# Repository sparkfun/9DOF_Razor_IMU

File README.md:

SparkFun 9DoF Razor IMU M0
========================================

[*SparkFun 9DoF Razor IMU M0 (SEN-14001)*](https://www.sparkfun.com/products/14001)

The [SparkFun 9DoF Razor IMU M0](https://www.sparkfun.com/products/14001) combines a [SAMD21](https://www.sparkfun.com/products/13664) microprocessor with an [MPU-9250](https://www.sparkfun.com/products/13762) 9DoF (nine degrees of freedom) sensor to create a tiny, re-programmable, multi-purpose inertial measurement unit (IMU). It can be programmed to monitor and log motion, transmit Euler angles over a serial port, or to even act as a step-counting pedometer.

The 9DoF Razor's MPU-9250 features three, three-axis sensors -- an accelerometer, gyroscope, and magnetometer -- which gives it the ability to sense linear acceleration, angular rotation velocity, and magnetic field vector's. The on-board microprocessor -- Atmel's [SAMD21G18A](http://www.atmel.com/devices/ATSAMD21G18.aspx) -- is an Arduino-compatible, 32-bit ARM Cortex-M0+ microcontroller also featured on the [Arduino Zero](https://www.arduino.cc/en/Main/ArduinoBoardZero) and [SAMD21 Mini Breakout](https://www.sparkfun.com/products/13664) boards.

Repository Contents
-------------------

* **/Documentation** - Data sheets, additional product information
* **/Firmware** - Example code 
* **/Hardware** - Eagle design files (.brd, .sch)
* **/Libraries** - Libraries for use with the 9DoF Razor IMU M0
* **/Production Files** - Production panel files (.brd)

Documentation
--------------
* **[SparkFun MPU-9250 DMP Arduino Library](https://github.com/sparkfun/SparkFun_MPU-9250-DMP_Arduino_Library)** - Arduino library for the 9DoF Razor IMU M0's MPU-9250, enabling the 9DoF's digital motion processor (DMP).
* **[Hookup Guide](https://learn.sparkfun.com/tutorials/9dof-razor-imu-m0-hookup-guide)** - Basic hookup guide for the 9DoF Razor IMU M0.
* **[SparkFun Fritzing repo](https://github.com/sparkfun/Fritzing_Parts)** - Fritzing diagrams for SparkFun products.
* **[SparkFun 3D Model repo](https://github.com/sparkfun/3D_Models)** - 3D models of SparkFun products. 

Product Versions
----------------
* [SparkFun 9DoF Razor IMU M0 (SEN-14001)](https://www.sparkfun.com/products/14001)- Latest release.
* [SparkFun 9DoF Razor IMU (SEN-10736)](https://www.sparkfun.com/products/retired/10736) - Initial release, featuring an ATmega328, ADXL345 (accelerometer), ITG-3200 (gyroscope), and HMC5883L (magnetometer).

Version History
---------------
* [V_3.0](https://github.com/sparkfun/9DOF_Razor_IMU/releases/tag/V_3.0) - Hardware and firmware files for version 3.0 -- released as SEN-14001.
* [V_2.3](https://github.com/sparkfun/9DOF_Razor_IMU/releases/tag/V_2.3) - Hardware and firmware design files for version 2.3 -- released as SEN-10736.

License Information
-------------------

This product is _**open source**_! 

Please review the LICENSE.md file for license information. 

If you have any questions or concerns on licensing, please contact techsupport@sparkfun.com.

Distributed as-is; no warranty is given.

- Your friends at SparkFun.

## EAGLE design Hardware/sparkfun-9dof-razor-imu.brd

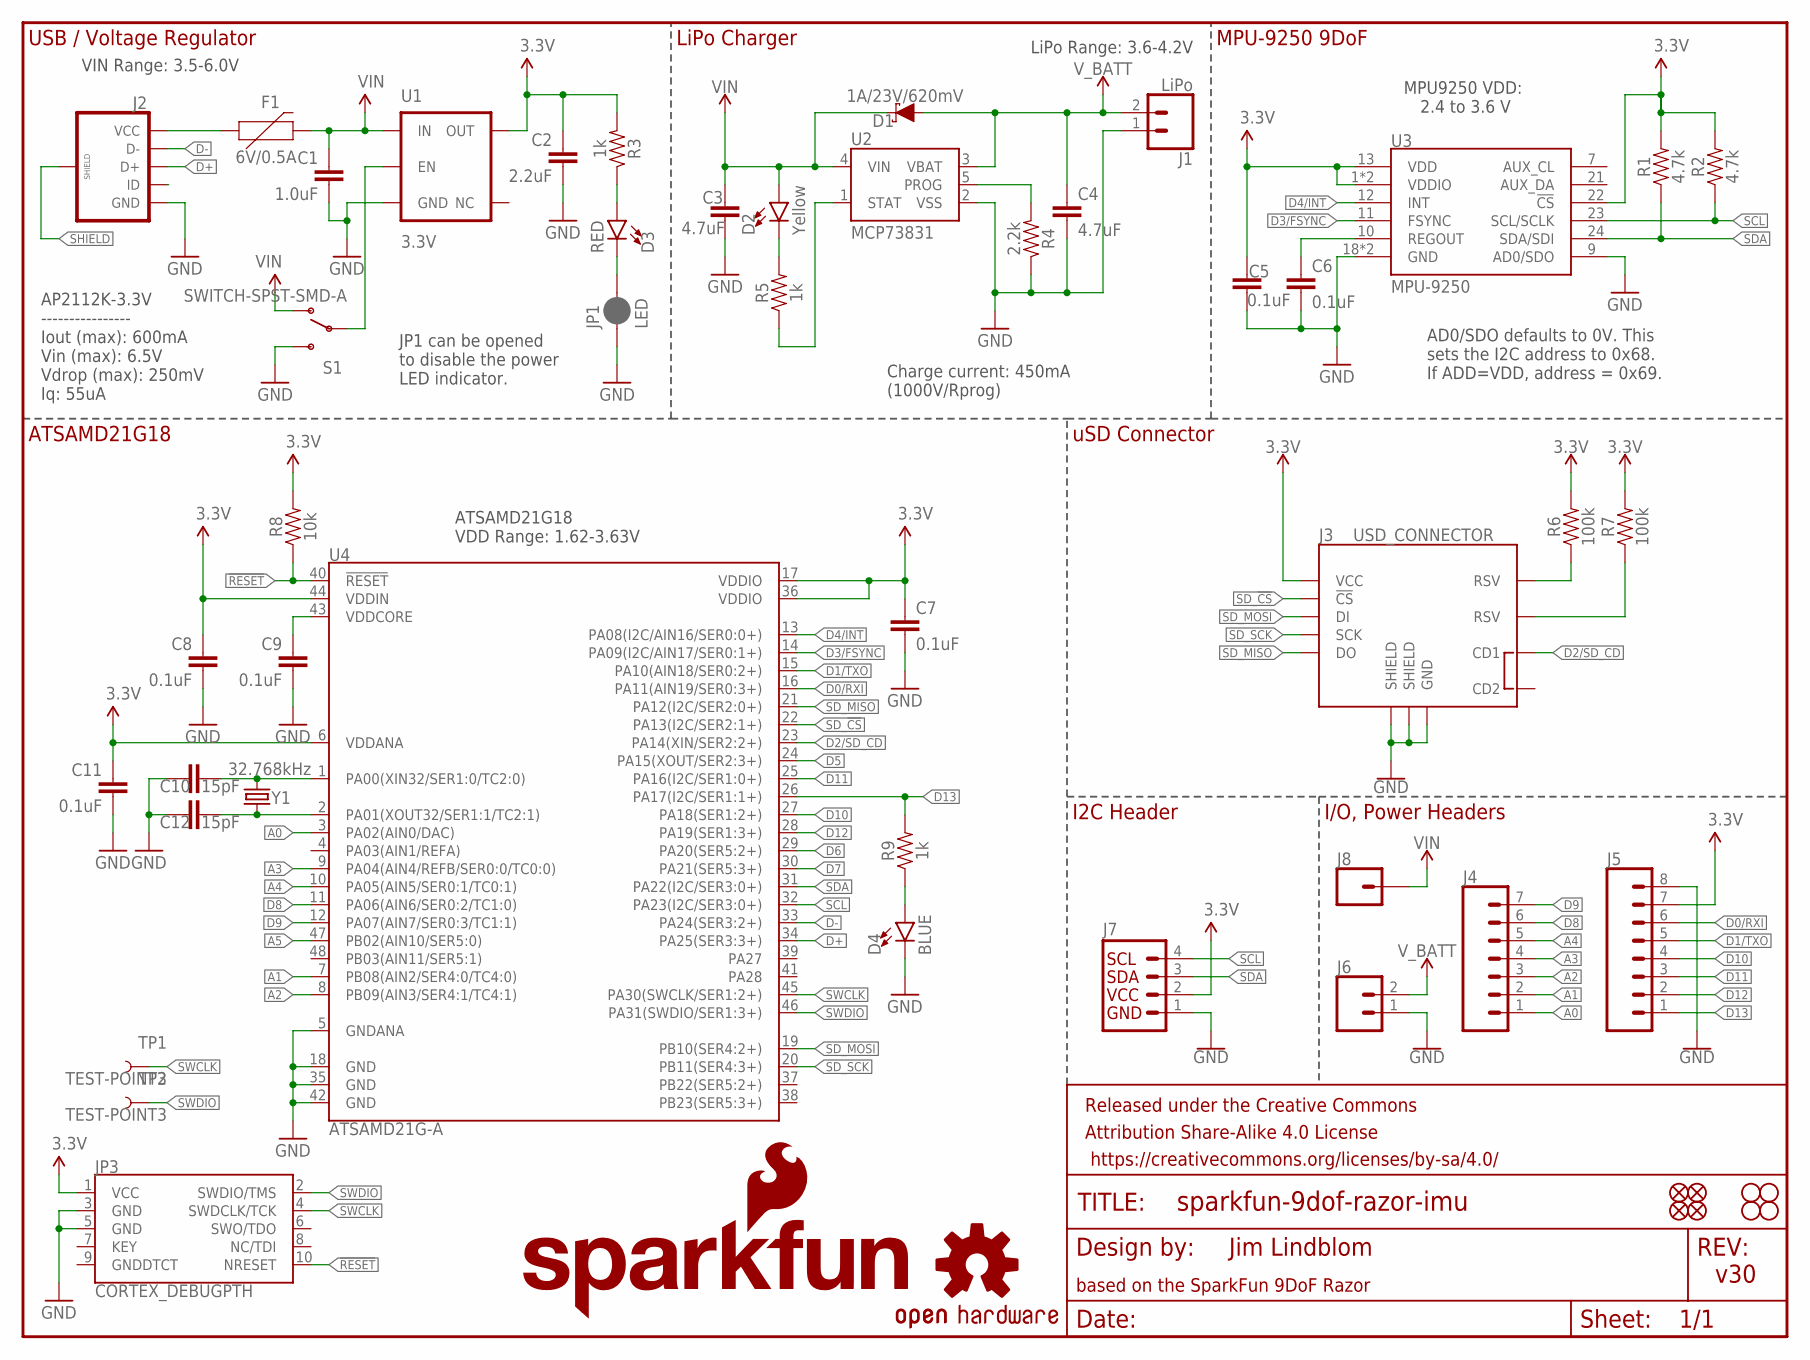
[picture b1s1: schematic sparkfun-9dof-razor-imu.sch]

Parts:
C1: 1.0uF; 0603
C2: 2.2uF; 0603
C3, C4: 4.7uF; 0603
C5, C6, C7, C8, C9, C11: 0.1uF; 0603
C10, C12: 15pF; 0603
D1: 1A/23V/620mV; SOD-323
D2: Yellow; LED-0603
D3: RED; LED-0603
D4: BLUE; LED-0603
F1: 6V/0.5A; 1206
FD1, FD2, FD3, FD4: FIDUCIAL1X2; FIDUCIAL-1X2
FRAME1: FRAME-LETTER; CREATIVE_COMMONS
H1, H2, H3, H4: STAND-OFF
J1: LiPo; JST-2-SMD
J2: USB_MICROB_PLUGCONN-11752; USB-B-MICRO-SMD_V03
J3: USD_CONNECTOR; MICRO-SD-SOCKET-PP
J4: CONN_07; 1X07
J5: CONN_08"; 1X08
J6: CONN_02; 1X02
J7: I2C_STANDARD; 1X04
J8: CONN_01; 1X01
JP1: LED; SMT-JUMPER_2_NC_PASTE_NO-SILK
JP3: CORTEX_DEBUGPTH; 2X5-PTH-1.27MM
LOGO1: SFE_LOGO_FLAME.1_INCH; SFE_LOGO_FLAME_.1
LOGO2: OSHW-LOGOS; OSHW-LOGO-S
LOGO3: SFE_LOGO_NAME.1_INCH; SFE_LOGO_NAME_.1
R1, R2: 4.7k; 0603
R3, R5, R9: 1k; 0603
R4: 2.2k; 0603
R6, R7: 100k; 0603
R8: 10k; 0603
S1: SWITCH-SPST-SMD-A
TP1, TP2: TEST-POINT3; PAD.03X.03
U1: 3.3V; SOT23-5
U2: MCP73831; SOT23-5
U3: MPU-9250; QFN24-3X3
U4: ATSAMD21G-A; TQFP-48
Y1: 32.768kHz; CRYSTAL-SMD-3.2X1.5MM

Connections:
3.3V: C2.1, C5.1, C7.1, C8.1, C11.1, J3.VCC, J5.7, J7.2, JP3.1 (VCC), R1.2, R2.2, R3.2, R6.2, R7.2, R8.2, U1.5 (OUT), U3.1 (VDDIO), U3.8 (VDDIO), U3.13 (VDD), U3.22 (!CS), U4.6 (VDDANA), U4.17 (VDDIO), U4.36 (VDDIO), U4.44 (VDDIN)
!RESET: JP3.10 (NRESET), R8.1, U4.40 (!RESET!)
A0: J4.1, U4.3 (PA02(AIN0/DAC))
A1: J4.2, U4.7 (PB08(AIN2/SER4:0/TC4:0))
A2: J4.3, U4.8 (PB09(AIN3/SER4:1/TC4:1))
A3: J4.4, U4.9 (PA04(AIN4/REFB/SER0:0/TC0:0))
A4: J4.5, U4.10 (PA05(AIN5/SER0:1/TC0:1))
A5: U4.47 (PB02(AIN10/SER5:0))
CHG_LED: R5.1, U2.1 (STAT)
D0/RXI: J5.6, U4.16 (PA11(AIN19/SER0:3+))
D1/TXO: J5.5, U4.15 (PA10(AIN18/SER0:2+))
D2/SD_CD: J3.CD1, U4.23 (PA14(XIN/SER2:2+))
D3/FSYNC: U3.11 (FSYNC), U4.14 (PA09(I2C/AIN17/SER0:1+))
D4/INT: U3.12 (INT), U4.13 (PA08(I2C/AIN16/SER0:0+))
D5: U4.24 (PA15(XOUT/SER2:3+))
D6: U4.29 (PA20(SER5:2+))
D7: U4.30 (PA21(SER5:3+))
D8: J4.6, U4.11 (PA06(AIN6/SER0:2/TC1:0))
D9: J4.7, U4.12 (PA07(AIN7/SER0:3/TC1:1))
D10: J5.4, U4.27 (PA18(SER1:2+))
D11: J5.3, U4.25 (PA16(I2C/SER1:0+))
D12: J5.2, U4.28 (PA19(SER1:3+))
D13: J5.1, R9.2, U4.26 (PA17(I2C/SER1:1+))
D+: J2.D+, U4.34 (PA25(SER3:3+))
D-: J2.D-, U4.33 (PA24(SER3:2+))
GND: C1.2, C2.2, C3.2, C4.2, C5.2, C6.2, C7.2, C8.2, C9.2, C10.1, C11.2, C12.2, D4.C, J1.1 (2), J2.GND, J3.GND, J3.GND1 (SHIELD), J3.GND3 (SHIELD), J5.8, J6.1, J7.1, JP1.1, JP3.3 (GND), JP3.5 (GND), R4.1, S1.3 (S), U1.2 (GND), U2.2 (VSS), U3.9 (AD0/SDO), U3.18 (GND), U3.20 (GND), U4.5 (GNDANA), U4.18 (GND), U4.35 (GND), U4.42 (GND)
ID: J2.ID
unnamed: F1.1, J2.VBUS (VCC)
unnamed: C10.2, U4.1 (PA00(XIN32/SER1:0/TC2:0)), Y1.P$2 (2)
unnamed: D4.A, R9.1
unnamed: C12.1, U4.2 (PA01(XOUT32/SER1:1/TC2:1)), Y1.P$1 (1)
unnamed: D3.A, R3.1
unnamed: R4.2, U2.5 (PROG)
unnamed: J3.RSV1 (RSV), R6.1
unnamed: J3.RSV2 (RSV), R7.1
unnamed: D2.C, R5.2
unnamed: D3.C, JP1.2
REGOUT: C6.1, U3.10 (REGOUT)
SCL: J7.4, R2.1, U3.23 (SCL/SCLK), U4.32 (PA23(I2C/SER3:0+))
SDA: J7.3, R1.1, U3.24 (SDA/SDI), U4.31 (PA22(I2C/SER3:0+))
SD_!CS!: J3.CS (!CS), U4.22 (PA13(I2C/SER2:1+))
SD_MISO: J3.DO, U4.21 (PA12(I2C/SER2:0+))
SD_MOSI: J3.DI, U4.19 (PB10(SER4:2+))
SD_SCK: J3.SCLK (SCK), U4.20 (PB11(SER4:3+))
SHIELD: J2.SHIELD1 (SHIELD), J2.SHIELD2 (SHIELD), J2.SHIELD3 (SHIELD)
SWCLK: JP3.4 (SWDCLK/TCK), TP1.P$1, U4.45 (PA30(SWCLK/SER1:2+))
SWDIO: JP3.2 (SWDIO/TMS), TP2.P$1, U4.46 (PA31(SWDIO/SER1:3+))
VDDCORE: C9.1, U4.43 (VDDCORE)
VIN: C1.1, C3.1, D1.C, D2.A, F1.2, J8.1, S1.1 (O), U1.1 (IN), U2.4 (VIN)
VREG_EN: S1.2, U1.3 (EN)
V_BATT: C4.1, D1.A, J1.2 (1), J6.2, U2.3 (VBAT)

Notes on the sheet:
AD0/SDO defaults to 0V. This sets the I2C address to 0x68. If ADD=VDD, address = 0x69.
MPU9250 VDD: 2.4 to 3.6 V
USB / Voltage Regulator
ATSAMD21G18 VDD Range: 1.62-3.63V
VIN Range: 3.5-6.0V
AP2112K-3.3V ---------------- Iout (max): 600mA Vin (max): 6.5V Vdrop (max): 250mV Iq: 55uA
v30
Jim Lindblom
ATSAMD21G18
LiPo Charger
MPU-9250 9DoF
uSD Connector
I2C Header
I/O, Power Headers
JP1 can be opened to disable the power LED indicator.
based on the SparkFun 9DoF Razor
LiPo Range: 3.6-4.2V
Charge current: 450mA (1000V/Rprog)

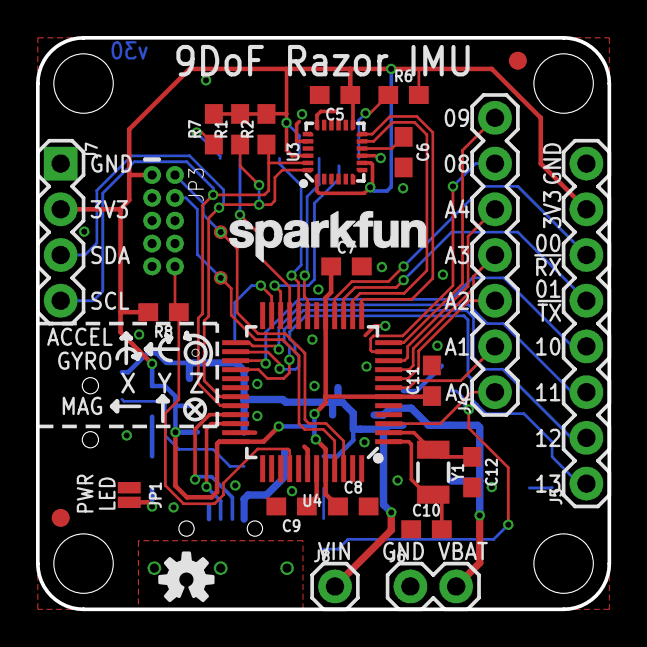
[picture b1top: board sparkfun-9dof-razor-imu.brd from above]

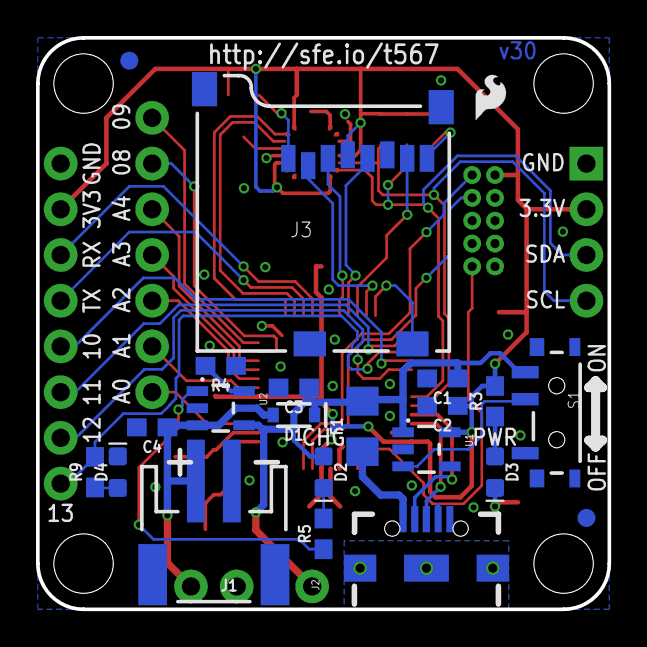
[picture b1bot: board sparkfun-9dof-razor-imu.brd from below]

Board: 2 copper layers, 31.8 x 31.8 mm, 56 parts (22 on the bottom side), 46 nets.

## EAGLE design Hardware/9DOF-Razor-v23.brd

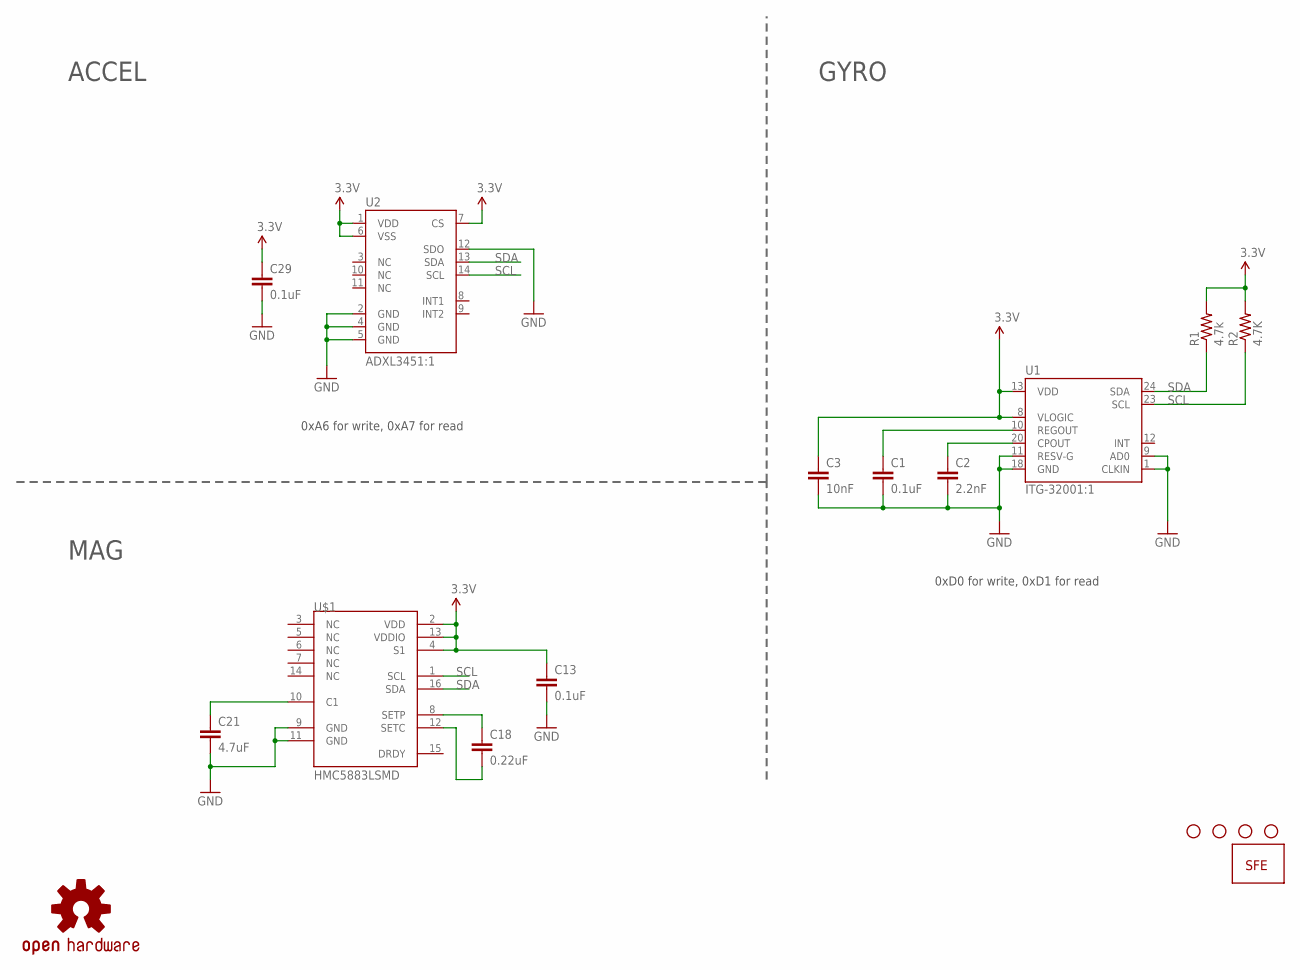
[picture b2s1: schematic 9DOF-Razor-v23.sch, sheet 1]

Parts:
C1, C13, C29: 0.1uF; 0603-CAP
C2: 2.2nF; 0603-CAP
C3: 10nF; 0603-CAP
C18: 0.22uF; 0603-CAP
C21: 4.7uF; 0603-CAP
JP2, JP4, JP5, JP6: STAND-OFF
JP3: LOGO-SFENEW; SFE-NEW-WEBLOGO
R1: 4.7k; 0603-RES
R2: 4.7K; 0603-RES
U1: ITG-32001:1; QFN-24_ITG3200_1:1
U2: ADXL3451:1; LGA14
U$1: HMC5883LSMD; 16LPCC
U$4: OSHW-LOGOL; OSHW-LOGO-L

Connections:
3.3V: C3.1, C13.1, C29.1, R1.2, R2.2, U1.8 (VLOGIC), U1.13 (VDD), U2.1 (VDD), U2.6 (VSS), U2.7 (CS), U$1.2 (VDD), U$1.4 (S1), U$1.13 (VDDIO); also elsewhere on the board
GND: C1.2, C2.2, C3.2, C13.2, C21.2, C29.2, U1.1 (CLKIN), U1.9 (AD0), U1.11 (RESV-G), U1.18 (GND), U2.2 (GND), U2.4 (GND), U2.5 (GND), U2.12 (SDO), U$1.9 (GND), U$1.11 (GND); also elsewhere on the board
unnamed: C18.2, U$1.8 (SETP)
unnamed: C18.1, U$1.12 (SETC)
unnamed: C1.1, U1.10 (REGOUT)
unnamed: C2.1, U1.20 (CPOUT)
unnamed: C21.1, U$1.10 (C1)
SCL: R2.1, U1.23 (SCL), U2.14 (SCL), U$1.1 (SCL); also elsewhere on the board
SDA: R1.1, U1.24 (SDA), U2.13 (SDA), U$1.16 (SDA); also elsewhere on the board

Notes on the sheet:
GYRO
ACCEL
MAG
0xD0 for write, 0xD1 for read
0xA6 for write, 0xA7 for read

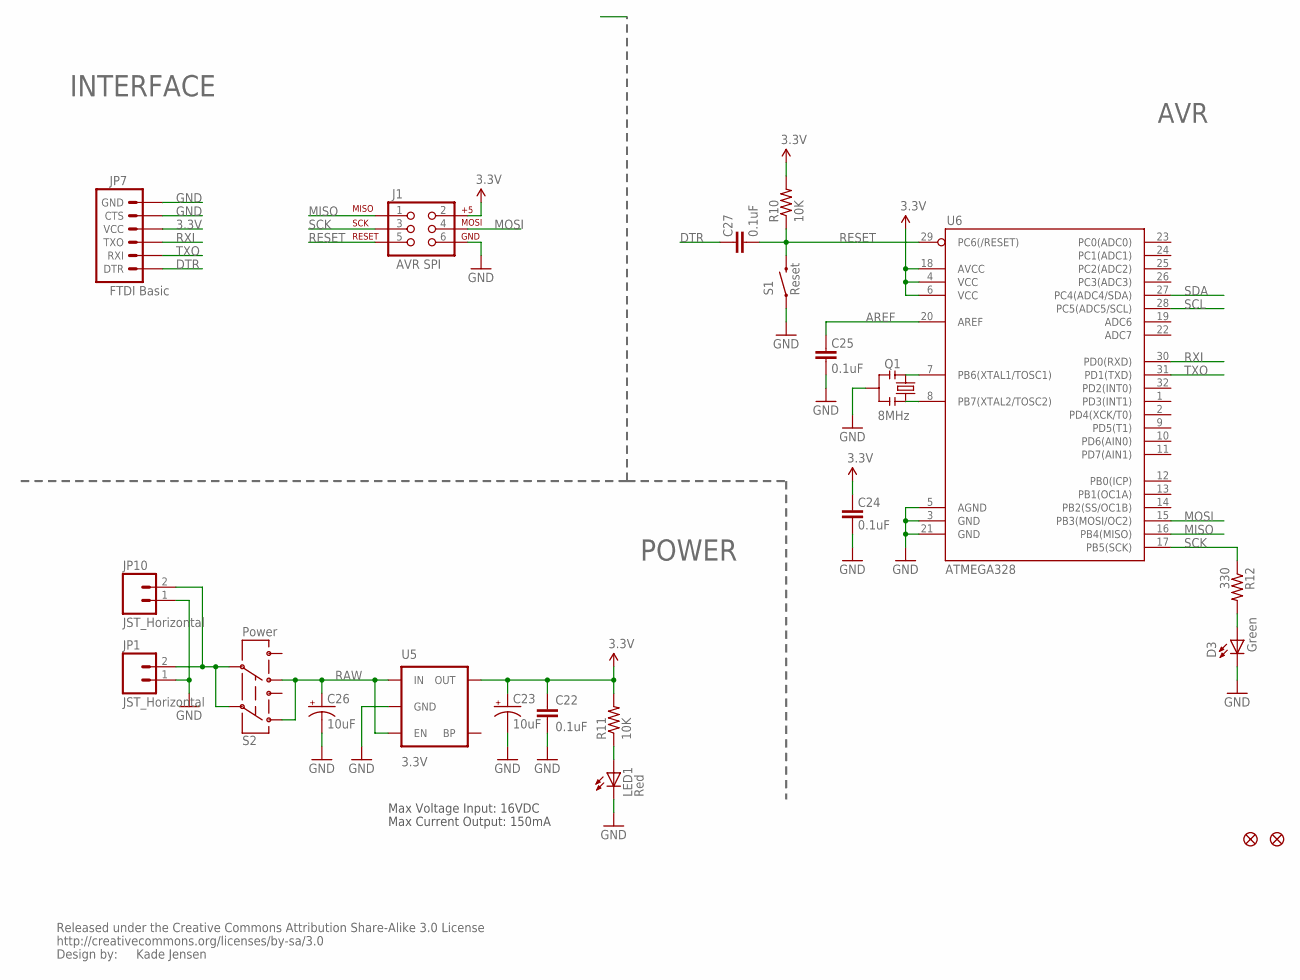
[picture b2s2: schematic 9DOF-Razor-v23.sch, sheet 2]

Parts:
C22, C24, C25, C27: 0.1uF; 0603-CAP
C23, C26: 10uF; EIA3216
D3: Green; LED-0603
J1: AVR_SPI_PRG_6PTH; 2X3
JP1: JST_Horizontal; JST-2-SMD
JP7: FTDI Basic; 1X06
JP10: JST_Horizontal; 1X02
JP11, JP12: FIDUCIAL1X2.5; FIDUCIAL-1X2.5
LED1: Red; LED-0603
Q1: 8MHz; RESONATOR-SMD
R10, R11: 10K; 0603-RES
R12: 330; 0603-RES
S1: Reset; TACTILE_SWITCH_SMD
S2: Power; AYZ0202
U5: 3.3V; SOT23-5
U6: ATMEGA328; TQFP32-08
U$3: CREATIVE_COMMONS

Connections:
3.3V: C22.1, C23.A (+), C24.2, J1.2, JP7.4 (VCC), R10.2, R11.2, U5.5 (OUT), U6.4 (VCC), U6.6 (VCC), U6.18 (AVCC); also elsewhere on the board
AREF: C25.2, U6.20 (AREF)
DTR: C27.2, JP7.1 (DTR)
GND: C22.2, C23.C (-), C24.1, C25.1, C26.C (-), D3.C, J1.6, JP1.1, JP7.5 (CTS), JP7.6 (GND), JP10.1, LED1.C, Q1.2, S1.1, U5.2 (GND), U6.3 (GND), U6.5 (AGND), U6.21 (GND); also elsewhere on the board
MISO: J1.1, U6.16 (PB4(MISO))
MOSI: J1.4, U6.15 (PB3(MOSI/OC2))
unnamed: D3.A, R12.2
unnamed: Q1.1, U6.8 (PB7(XTAL2/TOSC2))
unnamed: Q1.3, U6.7 (PB6(XTAL1/TOSC1))
unnamed: JP1.2, JP10.2, S2.2, S2.5
unnamed: LED1.A, R11.1
RAW: C26.A (+), S2.1, S2.4, U5.1 (IN), U5.3 (EN)
RESET: C27.1, J1.5, R10.1, S1.3 (2), U6.29 (PC6(/RESET))
RXI: JP7.3 (TXO), U6.30 (PD0(RXD))
SCK: J1.3, R12.1, U6.17 (PB5(SCK))
SCL: U6.28 (PC5(ADC5/SCL)); also elsewhere on the board
SDA: U6.27 (PC4(ADC4/SDA)); also elsewhere on the board
TXO: JP7.2 (RXI), U6.31 (PD1(TXD))

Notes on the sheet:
Max Voltage Input: 16VDC
Max Current Output: 150mA
AVR
INTERFACE
POWER
AVR SPI
Kade Jensen

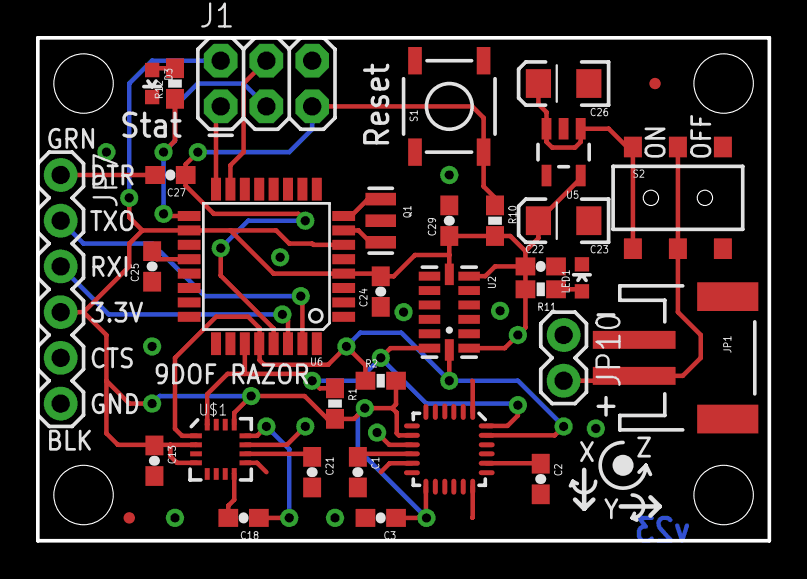
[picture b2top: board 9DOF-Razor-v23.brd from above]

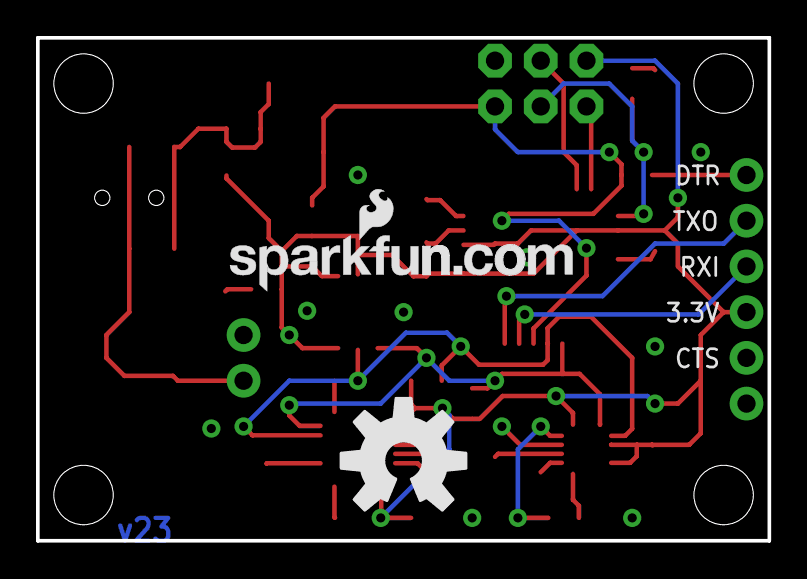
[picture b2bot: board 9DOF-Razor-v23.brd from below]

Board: 2 copper layers, 40.6 x 27.9 mm, 40 parts (2 on the bottom side), 23 nets.

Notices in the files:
parts and their libraries:
SparkFun: Released under the Creative Commons Attribution Share-Alike 3.0 License
SparkFun: http://creativecommons.org/licenses/by-sa/3.0
SparkFun-Capacitors: Licensing: Creative Commons ShareAlike 4.0 International - https://creativecommons.org/licenses/by-sa/4.0
